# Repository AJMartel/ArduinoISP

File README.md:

This is the Arduino programmer which turns the Arduino into an ISP for programming
chips, setting fuses and so on. It has a rescue function, which allows you to 
inject a clock signal via a pushbutton in the case you set the clock source
as external.

Eagle board and schematic enclosed.

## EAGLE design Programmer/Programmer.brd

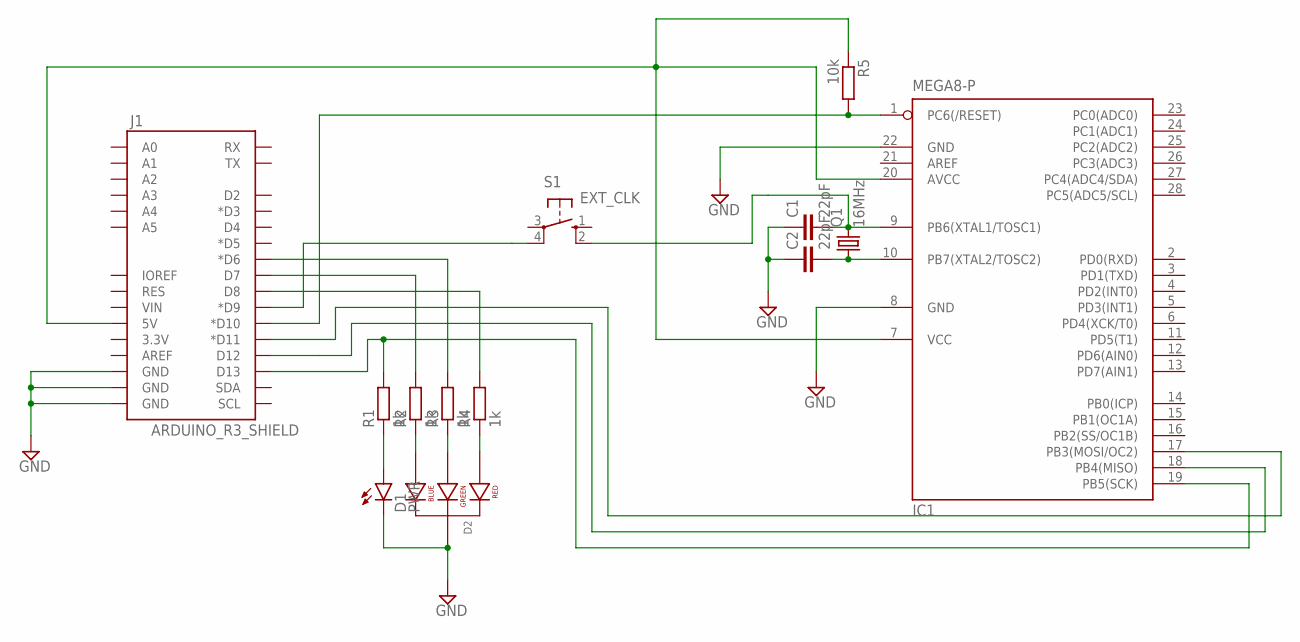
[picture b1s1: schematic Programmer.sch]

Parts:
C1, C2: 22pF; C5B2.5
D1: PWR; LED3MM
D2: LED-RGB-CC-THRUCLEAR; LED-RGB-THRU
IC1: MEGA8-P; DIL28-3
J1: ARDUINO_R3_SHIELD; UNO_R3_SHIELD
Q1: 16MHz; HC49/S
R1, R2, R3, R4: 1k; 0207/2V
R5: 10k; 0207/2V
S1: EXT_CLK; B3F-10XX

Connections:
GND: C1.1, C2.1, D1.K (C), D2.2 (CATHODE), IC1.8 (GND), IC1.22 (GND), J1.GND@0 (GND), J1.GND@1 (GND), J1.GND@2 (GND)
unnamed: C1.2, IC1.9 (PB6(XTAL1/TOSC1)), Q1.2, S1.2 (S1)
unnamed: D2.1 (RED_CATHODE), R4.1
unnamed: C2.2, IC1.10 (PB7(XTAL2/TOSC2)), Q1.1
unnamed: D1.A, R1.1
unnamed: D2.4 (BLUE_CATHODE), R2.1
unnamed: D2.3 (GREEN_CATHODE), R3.1
unnamed: J1.D6 (*D6), R3.2
unnamed: J1.D8, R4.2
unnamed: J1.D7, R2.2
unnamed: IC1.19 (PB5(SCK)), J1.D13, R1.2
unnamed: IC1.1 (PC6(/RESET)), J1.D10 (*D10), R5.2
unnamed: IC1.18 (PB4(MISO)), J1.D12
unnamed: IC1.17 (PB3(MOSI/OC2)), J1.D11 (*D11)
unnamed: J1.D9 (*D9), S1.4 (P1)
VCC: IC1.7 (VCC), IC1.20 (AVCC), J1.5V, R5.1

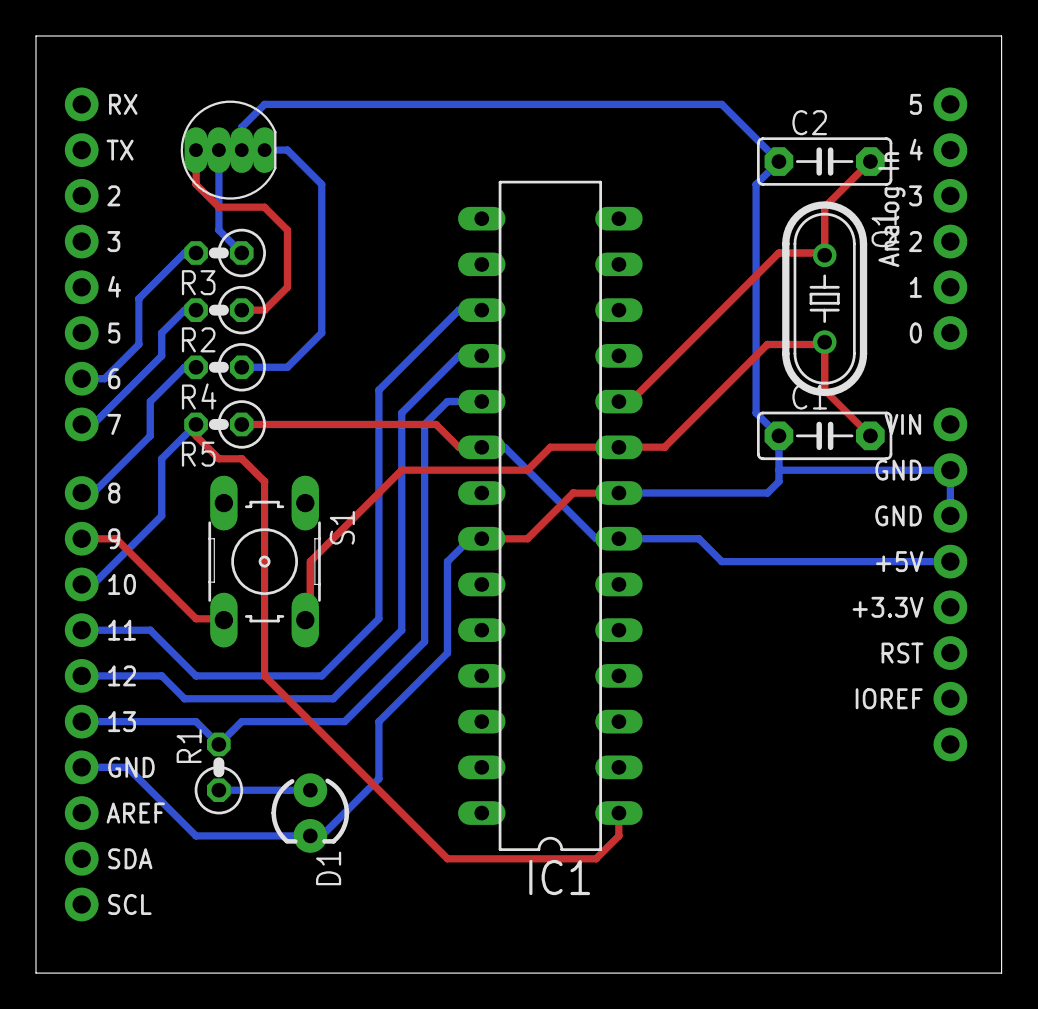
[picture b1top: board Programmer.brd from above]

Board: 2 copper layers, 53.6 x 52.1 mm, 13 parts (0 on the bottom side), 16 nets.

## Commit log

2015-07-23 Initial version
2015-07-23 Eagle board design
2015-07-26 Add Ebay URL
2016-07-13 Remove Ebay link (no longer for sale)

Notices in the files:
parts and their libraries:
SparkFun-Boards: Licensing: Creative Commons ShareAlike 4.0 International - https://creativecommons.org/licenses/by-sa/4.0
